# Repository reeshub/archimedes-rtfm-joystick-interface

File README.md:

# Acorn Archimedes RTFM Joystick Interface

**Current Status:** Gathering information.

Documenting all of the information I can get my hands on regarding the Acorn Archimedes RTFM joystick interface, a commercially-available expansion which plugs into the Econet port and provides 2x Atari-compatible 9-pin joystick ports.

The interface was compatible with all Archimedes machines and supported by [a large number of games on the system](https://forums.jaspp.org.uk/forum/viewtopic.php?f=25&t=399). Longer-term, I'd also like to document the Acorn parallel port interface so that all bases will be covered.

Some further information on the RTFM can be found here: [https://www.retro-kit.co.uk/page.cfm/content/RTFM-Joystick-interface/](https://www.retro-kit.co.uk/page.cfm/content/RTFM-Joystick-interface/)

## Clone Board By Darren Shepherd

The RTFM was a commercially available product, however [Darren Shepherd](http://dshepherd.co.uk/) has drawn up the schematics in [Autodesk Eagle](https://www.autodesk.com/products/eagle/overview) and had his own boards produced, which he has given permission to share here.

Pictured above: Darren's RTFM clone fitted to his Archimedes A3000. Note that he has interfaced it with the internal 9-pin port [using a modified version of this interface](http://qubeserver.com/qube/projects/a3000joyport.html).

For now, I'll include Darren's CAD files below. These are designed for use with [Autodesk Eagle](https://www.autodesk.com/products/eagle/overview) and are compatible with the free version.

## Bill Of Materials (Work In Progress)
- PCB
- 2.54mm Pin Header
- 2x SN74LS240N Octal Buffer / Line Driver IC
- 1x SN74LS32N Quadruple 2-Input Positive-OR Gate IC
- 2x Resistor Ladder (values TBC)
- 2x DE-9 male connector

## Downloads

- [RTFMJoy_zip,a91.dat](Darren%20Shepherd/RTFMJoy_zip,a91.dat) - Original driver software.
- [RTFMProject.rar](Darren%20Shepherd/RTFMProject.rar) - Version 1 PCB CAD package (superceded by v2 below).
    - [RTFM_2019-03-25.zip](Darren%20Shepherd/RTFMProject/RTFM_2019-03-25.zip) - Drill and Gerber files taken from the above for fabrication (superceded by v2 below).
- [RTFM2Project.rar](Darren%20Shepherd/RTFM2Project.rar) - Version 2 PCB CAD package.
    - [RTFM_201909151949.zip](Darren%20Shepherd/RTFM2Project/RTFM_201909151949.zip) - Drill and Gerber files taken from the above for fabrication.

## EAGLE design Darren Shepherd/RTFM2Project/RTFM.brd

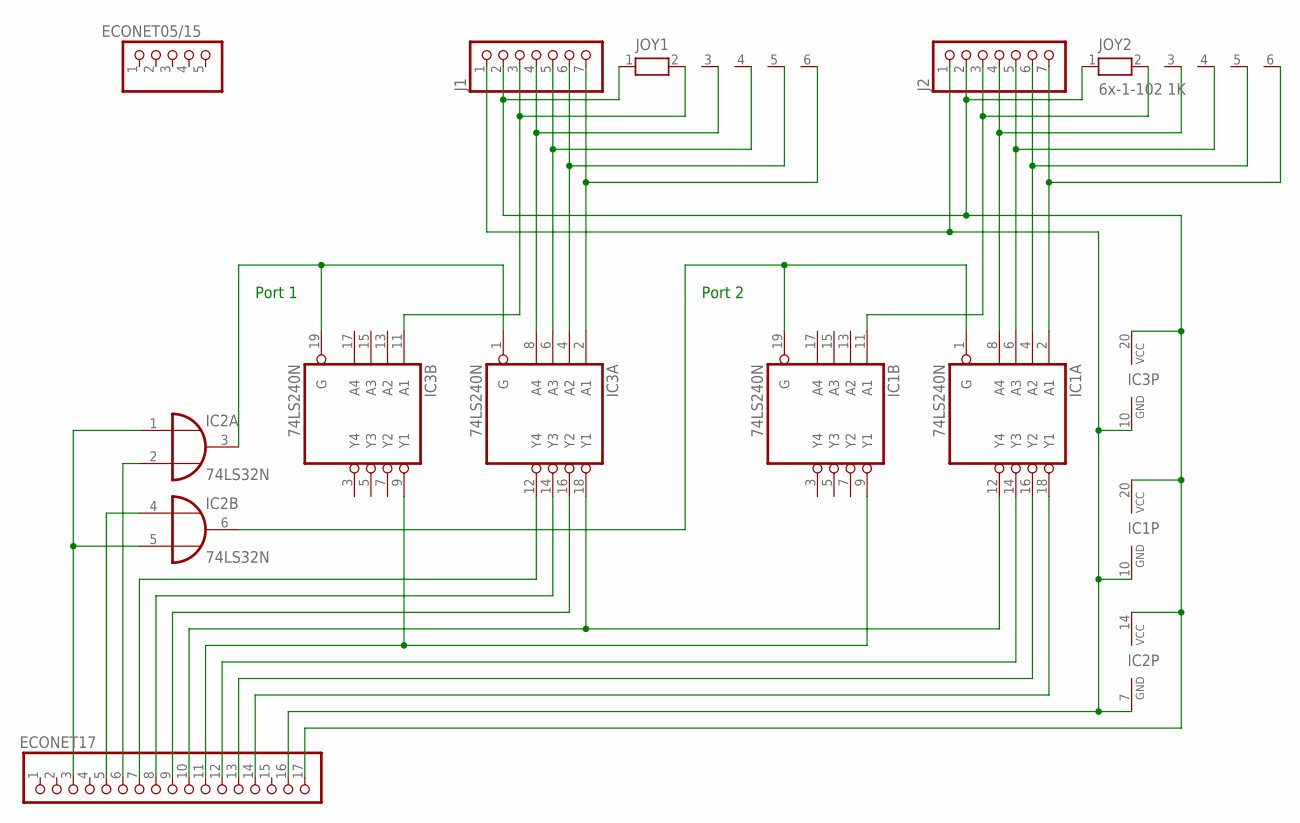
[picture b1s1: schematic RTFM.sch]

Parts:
ECONET05/15: PINHD-1X5; 1X05
ECONET17: PINHD-1X17; 1X17
IC1, IC3: 74LS240N; DIL20
IC2: 74LS32N; DIL14
J1, J2: PINHD-1X7; 1X07
JOY1, JOY2: 6x-1-102 1K; RN-6

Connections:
unnamed: ECONET17.3, IC2.1 (I0), IC2.5 (I1)
unnamed: ECONET17.5, IC2.4 (I0)
unnamed: ECONET17.6, IC2.2 (I1)
unnamed: IC1.1 (G), IC1.19 (G), IC2.6 (O)
unnamed: ECONET17.16, IC1.10 (GND), IC2.7 (GND), IC3.10 (GND), J1.1, J2.1
unnamed: ECONET17.7, IC3.12 (Y4)
unnamed: ECONET17.8, IC3.14 (Y3)
unnamed: ECONET17.9, IC3.16 (Y2)
unnamed: ECONET17.10, IC1.12 (Y4), IC3.18 (Y1)
unnamed: ECONET17.11, IC1.9 (Y1), IC3.9 (Y1)
unnamed: ECONET17.12, IC1.14 (Y3)
unnamed: ECONET17.13, IC1.16 (Y2)
unnamed: ECONET17.14, IC1.18 (Y1)
unnamed: ECONET17.17, IC1.20 (VCC), IC2.14 (VCC), IC3.20 (VCC), J1.2, J2.2, JOY1.1, JOY2.1
unnamed: IC3.4 (A2), J1.6, JOY1.5
unnamed: IC3.6 (A3), J1.5, JOY1.4
unnamed: IC3.8 (A4), J1.4, JOY1.3
unnamed: IC3.2 (A1), J1.7, JOY1.6
unnamed: IC1.2 (A1), J2.7, JOY2.6
unnamed: IC1.4 (A2), J2.6, JOY2.5
unnamed: IC1.6 (A3), J2.5, JOY2.4
unnamed: IC1.8 (A4), J2.4, JOY2.3
unnamed: IC1.11 (A1), J2.3, JOY2.2
unnamed: IC2.3 (O), IC3.1 (G), IC3.19 (G)
unnamed: IC3.11 (A1), J1.3, JOY1.2

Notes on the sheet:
Port 1
Port 2

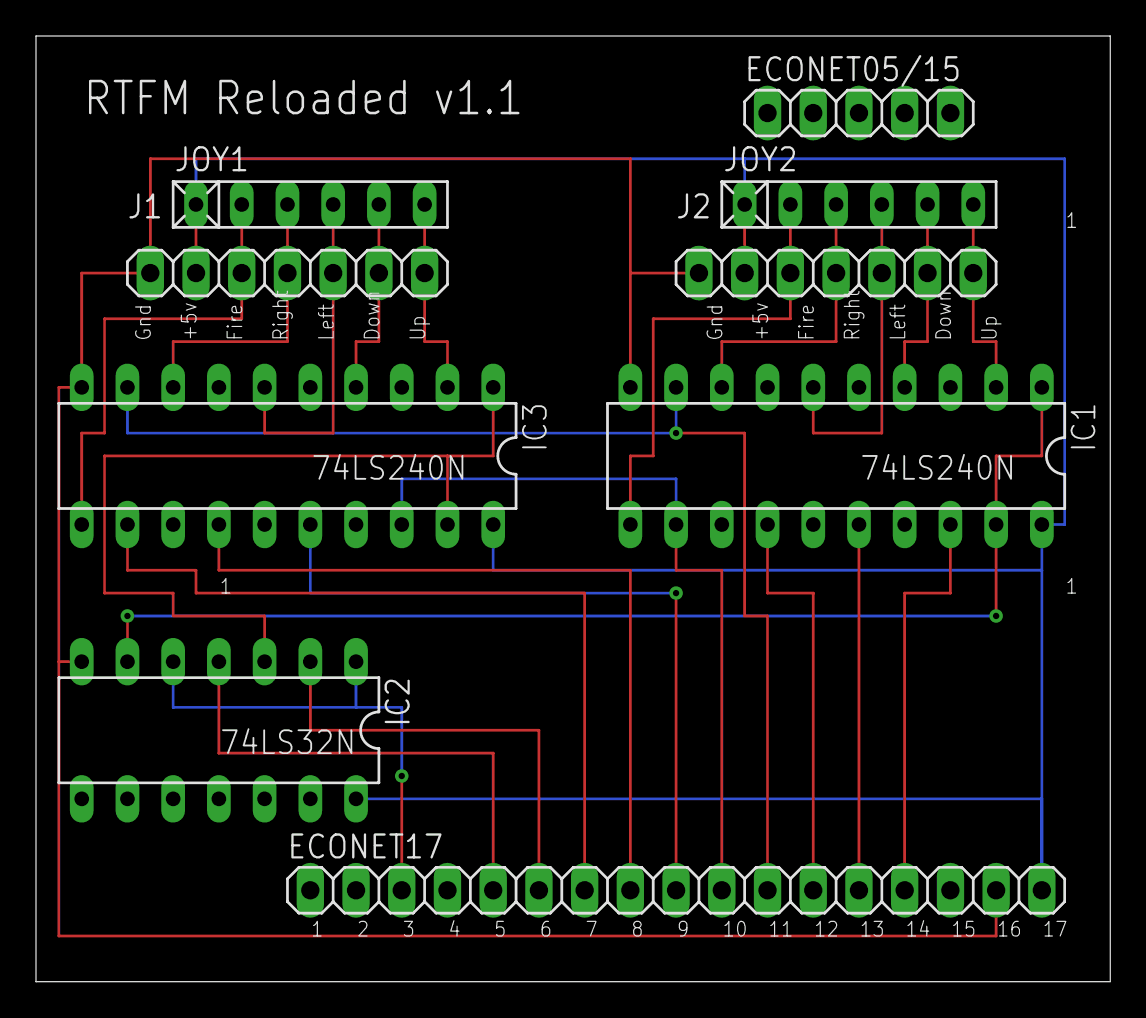
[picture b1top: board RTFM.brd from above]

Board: 2 copper layers, 59.7 x 52.5 mm, 9 parts (0 on the bottom side), 25 nets.

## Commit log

2020-08-28 Initial Commit - Info Emailed By Darren & Xavier
2020-08-29 Added Link To A3000 Serial Port Adapter
